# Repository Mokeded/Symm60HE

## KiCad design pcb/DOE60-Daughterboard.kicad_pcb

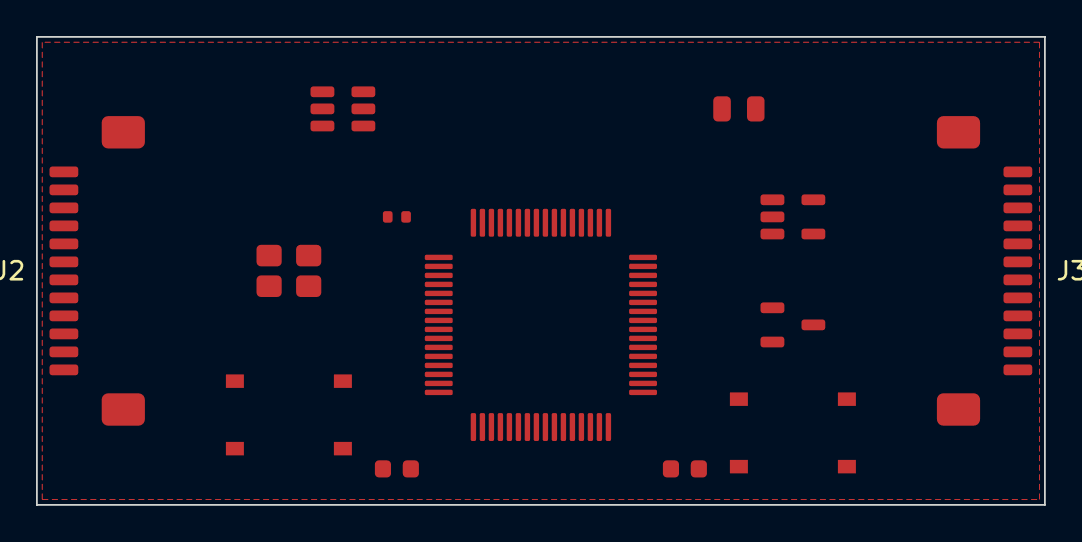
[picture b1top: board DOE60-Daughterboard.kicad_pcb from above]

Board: 2 copper layers, 56.0 x 26.0 mm, 13 parts (0 on the bottom side), 22 nets, no tracks yet.

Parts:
C1: 10u; C148_C_0603_1608Metric
C2: 1u; C148_C_0603_1608Metric
F1: 0.5A; F1_Fuse_0805_2012Metric
J2, J3: FFC_12P; FFC_12P_1.00mm_TopContact
R1: 12k; R3_R_0402_1005Metric
SW1, SW2: TS-1187A; SW1_SW_Push_1P1T_XKB_TS-1187A
U1: AT32F405RCT7; U4_LQFP-64_10x10mm_P0.5mm
U2: USBLC6-2SC6; U1_SOT-23-6
U3: TLV75733PDBV; U2_SOT-23-5
U4: XC6206P332MR; U3_SOT-23-3
Y1: 12MHz; Y1_Crystal_SMD_3225-4Pin_3.2x2.5mm

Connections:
+3V3A: J2.1, J3.1, U1.13, U4.2
+3V3D: C2.1, U1.1, U1.36, U3.5, U4.3
ADC_L1: J2.7, U1.17
ADC_L2: J2.9, U1.20
ADC_L3: J2.11, U1.21
ADC_L4: J2.12, U1.22
ADC_R1: J3.7, U1.23
ADC_R2: J3.9, U1.24
ADC_R3: J3.11, U1.25
ADC_R4: J3.12, U1.26
BOOT0: SW1.1, U1.60
GND: C1.2, C2.2, J2.2, J2.6, J2.8, J2.10, J3.2, J3.6, J3.8, J3.10, R1.2, SW1.2, SW2.2, U1.12, U1.31, U2.2, U3.2, U4.1, Y1.2, Y1.4
MUX_A0: J2.3, J3.3, U1.9
MUX_A1: J2.4, J3.4, U1.10
MUX_A2: J2.5, J3.5, U1.11
NRST: SW2.1, U1.7
USB_DM: U1.34, U2.3, U2.4
USB_DP: U1.35, U2.1, U2.6
USB_R: R1.1, U1.33
VBUS: C1.1, F1.2, U2.5, U3.1
XTAL_IN: U1.5, Y1.1
XTAL_OUT: U1.6, Y1.3

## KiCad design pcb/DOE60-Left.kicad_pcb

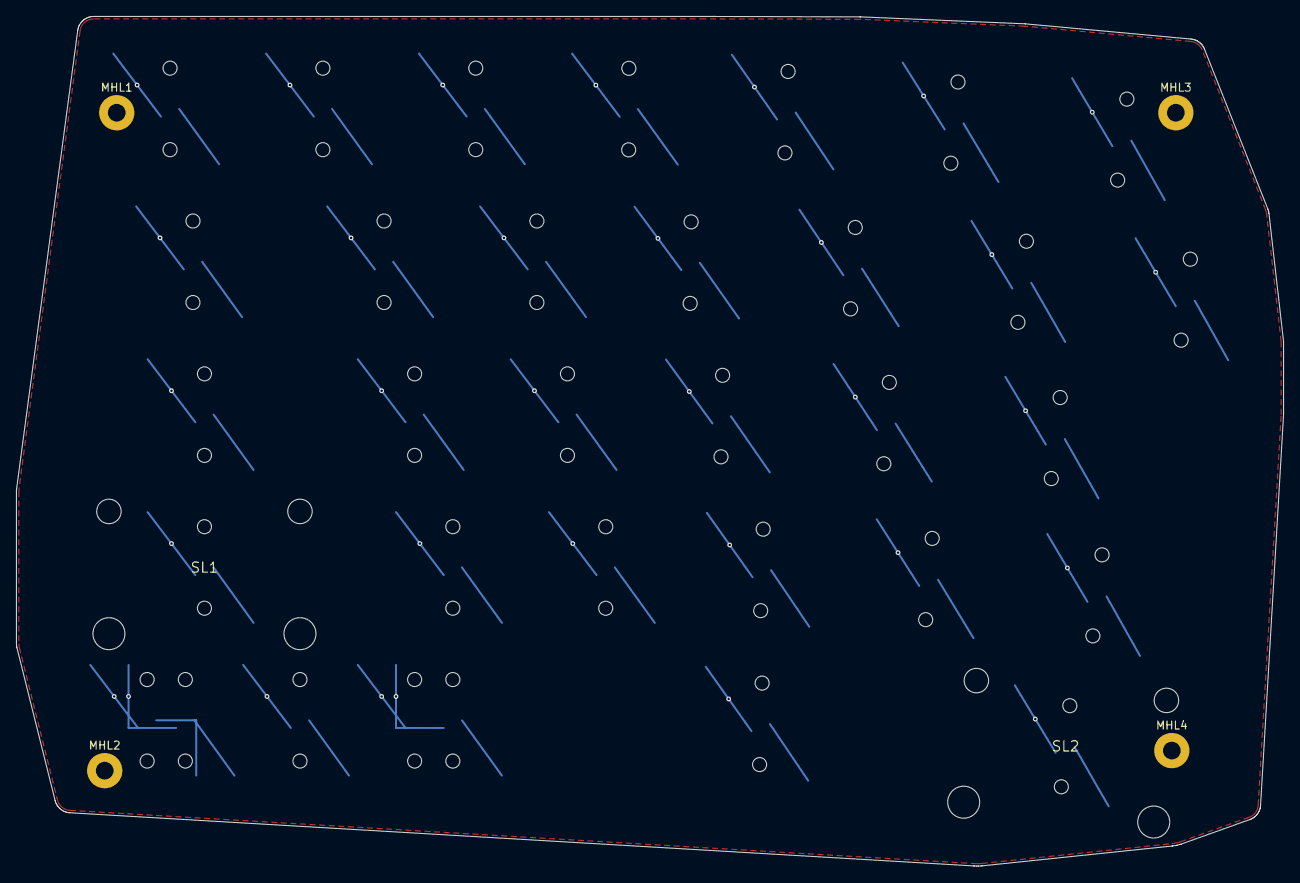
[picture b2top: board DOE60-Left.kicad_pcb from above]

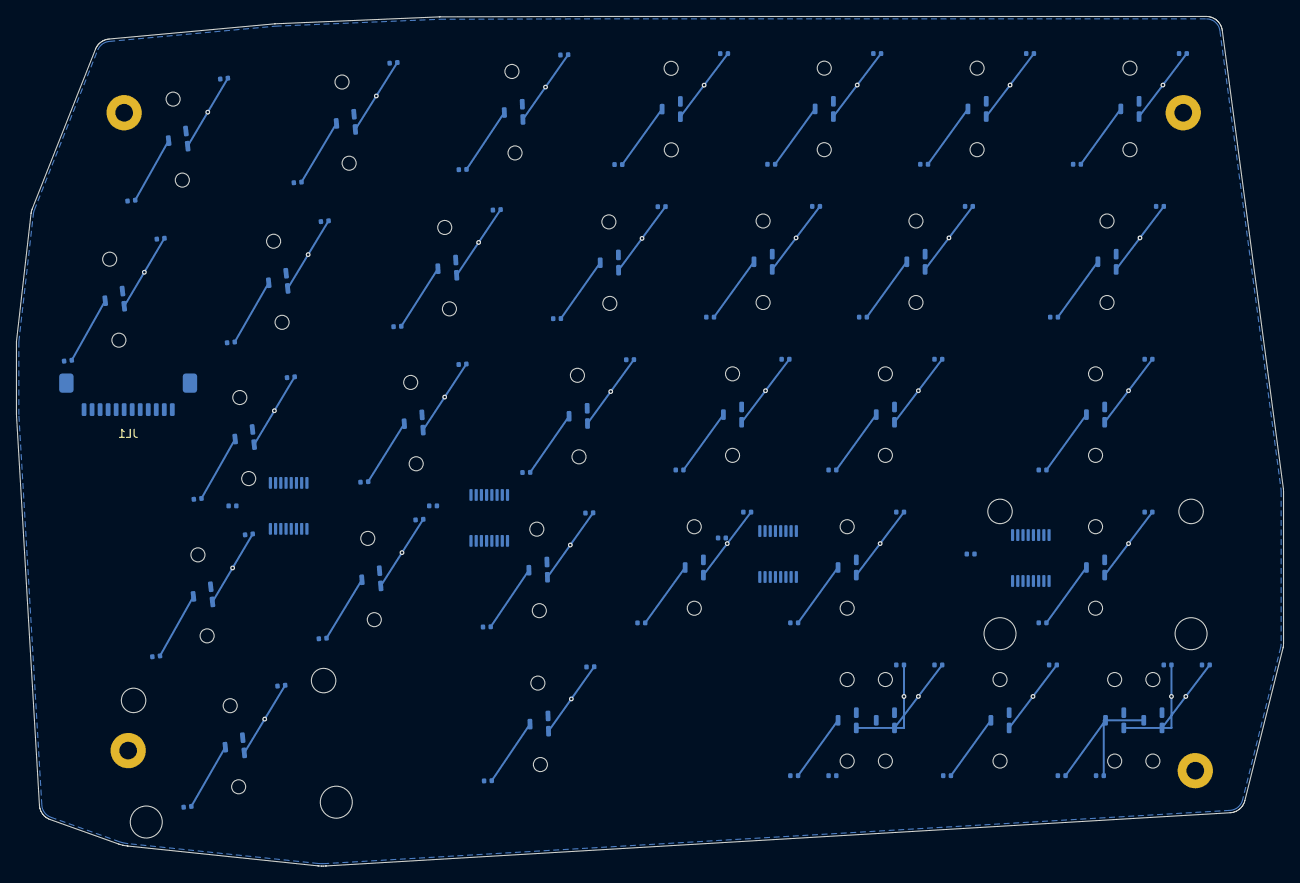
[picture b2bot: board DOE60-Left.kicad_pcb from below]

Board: 2 copper layers, 157.9 x 105.9 mm, 114 parts (108 on the bottom side), 40 nets.

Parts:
AML1, AML2, AML3, AML4: SN74LV4051A; AM1_TSSOP-16_4.4x5mm_P0.65mm
CL1A, CL2A, CL3A, CL4A, CL5A, CL6A, CL7A, CL8A, CL9A, CL10A, CL11A, CL12A, CL13A, CL14A, CL15A, CL16A, CL17A, CL18A, CL19A, CL20A, CL21A, CL22A, CL23A, CL24A, CL25A, CL26A, CL27A, CL28A, CL29A, CL30A, CL31A, CL32A, CL33A: 100n; C1_C_0402_1005Metric
CL1B, CL2B, CL3B, CL4B, CL5B, CL6B, CL7B, CL8B, CL9B, CL10B, CL11B, CL12B, CL13B, CL14B, CL15B, CL16B, CL17B, CL18B, CL19B, CL20B, CL21B, CL22B, CL23B, CL24B, CL25B, CL26B, CL27B, CL28B, CL29B, CL30B, CL31B, CL32B, CL33B: 4.7n; C1_C_0402_1005Metric
CML1, CML2, CML3, CML4: 100n; C1_C_0402_1005Metric
HEL1, HEL2, HEL3, HEL4, HEL5, HEL6, HEL7, HEL9, HEL10, HEL11, HEL12, HEL13, HEL14, HEL16, HEL17, HEL18, HEL19, HEL20, HEL22, HEL23, HEL24, HEL25, HEL26, HEL27, HEL29, HEL31: MT9102ET; HE_KEY_1.00u
HEL8, HEL28, HEL30, HEL32: MT9102ET; HE_KEY_1.50u
HEL15: MT9102ET; HE_KEY_1.75u
HEL21, HEL33: MT9102ET; HE_KEY_2.25u
JL1: FFC_12P; FFC_12P_1.00mm_TopContact
MHL1, MHL2, MHL3, MHL4: M2; MountingHole_2.2mm_M2_Pad
SL1, SL2: STAB_MX; STABILIZER_MX_2U

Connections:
+3V3A: AML1.16, AML2.16, AML3.16, AML4.16, CL1A.1, CL2A.1, CL3A.1, CL4A.1, CL5A.1, CL6A.1, CL7A.1, CL8A.1, CL9A.1, CL10A.1, CL11A.1, CL12A.1, CL13A.1, CL14A.1, CL15A.1, CL16A.1, CL17A.1, CL18A.1, CL19A.1, CL20A.1, CL21A.1, CL22A.1, CL23A.1, CL24A.1, CL25A.1, CL26A.1, CL27A.1, CL28A.1, CL29A.1, CL30A.1, CL31A.1, CL32A.1, CL33A.1, CML1.1, CML2.1, CML3.1, CML4.1, HEL1.1, HEL2.1, HEL3.1, HEL4.1, HEL5.1, HEL6.1, HEL7.1, HEL8.1, HEL9.1, HEL10.1, HEL11.1, HEL12.1, HEL13.1, HEL14.1, HEL15.1, HEL16.1, HEL17.1, HEL18.1, HEL19.1, HEL20.1, HEL21.1, HEL22.1, HEL23.1, HEL24.1, HEL25.1, HEL26.1, HEL27.1, HEL28.1, HEL29.1, HEL30.1, HEL31.1, HEL32.1, HEL33.1, JL1.1
ADC_L1: AML1.3, JL1.7
ADC_L2: AML2.3, JL1.9
ADC_L3: AML3.3, JL1.11
ADC_L4: AML4.3, JL1.12
GND: AML1.6, AML1.7, AML1.8, AML2.6, AML2.7, AML2.8, AML3.6, AML3.7, AML3.8, AML4.4, AML4.6, AML4.7, AML4.8, CL1A.2, CL1B.2, CL2A.2, CL2B.2, CL3A.2, CL3B.2, CL4A.2, CL4B.2, CL5A.2, CL5B.2, CL6A.2, CL6B.2, CL7A.2, CL7B.2, CL8A.2, CL8B.2, CL9A.2, CL9B.2, CL10A.2, CL10B.2, CL11A.2, CL11B.2, CL12A.2, CL12B.2, CL13A.2, CL13B.2, CL14A.2, CL14B.2, CL15A.2, CL15B.2, CL16A.2, CL16B.2, CL17A.2, CL17B.2, CL18A.2, CL18B.2, CL19A.2, CL19B.2, CL20A.2, CL20B.2, CL21A.2, CL21B.2, CL22A.2, CL22B.2, CL23A.2, CL23B.2, CL24A.2, CL24B.2, CL25A.2, CL25B.2, CL26A.2, CL26B.2, CL27A.2, CL27B.2, CL28A.2, CL28B.2, CL29A.2, CL29B.2, CL30A.2, CL30B.2, CL31A.2, CL31B.2, CL32A.2, CL32B.2, CL33A.2, CL33B.2, CML1.2, CML2.2, CML3.2, CML4.2, HEL1.2, HEL2.2, HEL3.2, HEL4.2, HEL5.2, HEL6.2, HEL7.2, HEL8.2, HEL9.2, HEL10.2, HEL11.2, HEL12.2, HEL13.2, HEL14.2, HEL15.2, HEL16.2, HEL17.2, HEL18.2, HEL19.2, HEL20.2, HEL21.2, HEL22.2, HEL23.2, HEL24.2, HEL25.2, HEL26.2, HEL27.2, HEL28.2, HEL29.2, HEL30.2, HEL31.2, HEL32.2, HEL33.2, JL1.2, JL1.6, JL1.8, JL1.10, MHL1.1, MHL2.1, MHL3.1, MHL4.1
HE_L01: AML1.13, CL1B.1, HEL1.3
HE_L02: AML1.14, CL2B.1, HEL2.3
HE_L03: AML1.15, CL3B.1, HEL3.3
HE_L04: AML1.12, CL4B.1, HEL4.3
HE_L05: AML1.1, CL5B.1, HEL5.3
HE_L06: AML1.5, CL6B.1, HEL6.3
HE_L07: AML1.2, CL7B.1, HEL7.3
HE_L08: AML1.4, CL8B.1, HEL8.3
HE_L09: AML2.13, CL9B.1, HEL9.3
HE_L10: AML2.14, CL10B.1, HEL10.3
HE_L11: AML2.15, CL11B.1, HEL11.3
HE_L12: AML2.12, CL12B.1, HEL12.3
HE_L13: AML2.1, CL13B.1, HEL13.3
HE_L14: AML2.5, CL14B.1, HEL14.3
HE_L15: AML2.2, CL15B.1, HEL15.3
HE_L16: AML2.4, CL16B.1, HEL16.3
HE_L17: AML3.13, CL17B.1, HEL17.3
HE_L18: AML3.14, CL18B.1, HEL18.3
HE_L19: AML3.15, CL19B.1, HEL19.3
HE_L20: AML3.12, CL20B.1, HEL20.3
HE_L21: AML3.1, CL21B.1, HEL21.3
HE_L22: AML3.5, CL22B.1, HEL22.3
HE_L23: AML3.2, CL23B.1, HEL23.3
HE_L24: AML3.4, CL24B.1, HEL24.3
HE_L25: AML4.13, CL25B.1, HEL25.3
HE_L26: AML4.14, CL26B.1, HEL26.3
HE_L27: AML4.15, CL27B.1, CL28B.1, HEL27.3, HEL28.3
HE_L28: AML4.12, CL29B.1, CL30B.1, HEL29.3, HEL30.3
HE_L29: AML4.1, CL31B.1, HEL31.3
HE_L30: AML4.5, CL32B.1, HEL32.3
HE_L31: AML4.2, CL33B.1, HEL33.3
MUX_A0: AML1.11, AML2.11, AML3.11, AML4.11, JL1.3
MUX_A1: AML1.10, AML2.10, AML3.10, AML4.10, JL1.4
MUX_A2: AML1.9, AML2.9, AML3.9, AML4.9, JL1.5

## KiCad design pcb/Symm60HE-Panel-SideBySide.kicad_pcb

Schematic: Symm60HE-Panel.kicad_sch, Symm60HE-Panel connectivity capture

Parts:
L-AML1, L-AML2, L-AML3, L-AML4, L-AML5: SN74LV4051A; AM1_TSSOP-16_4.4x5mm_P0.65mm
L-CL1A, L-CL2A, L-CL3A, L-CL4A, L-CL5A, L-CL6A, L-CL7A, L-CL8A, L-CL9A, L-CL10A, L-CL11A, L-CL12A, L-CL13A, L-CL14A, L-CL15A, L-CL16A, L-CL17A, L-CL18A, L-CL19A, L-CL20A, L-CL21A, L-CL22A, L-CL23A, L-CL24A, L-CL25A, L-CL26A, L-CL27A, L-CL28A, L-CL29A, L-CL30A, L-CL31A, L-CL32A, L-CL33A: 100n; C1_C_0402_1005Metric
L-CL1B, L-CL2B, L-CL3B, L-CL4B, L-CL5B, L-CL6B, L-CL7B, L-CL8B, L-CL9B, L-CL10B, L-CL11B, L-CL12B, L-CL13B, L-CL14B, L-CL15B, L-CL16B, L-CL17B, L-CL18B, L-CL19B, L-CL20B, L-CL21B, L-CL22B, L-CL23B, L-CL24B, L-CL25B, L-CL26B, L-CL27B, L-CL28B, L-CL29B, L-CL30B, L-CL31B, L-CL32B, L-CL33B: 4.7n; C1_C_0402_1005Metric
L-CML1, L-CML2, L-CML3, L-CML4, L-CML5: 100n; C1_C_0402_1005Metric
L-CRGBL1, L-CRGBL2, L-CRGBL3, L-CRGBL4, L-CRGBL5, L-CRGBL6, L-CRGBL7, L-CRGBL8, L-CRGBL9, L-CRGBL10, L-CRGBL11, L-CRGBL12, L-CRGBL13, L-CRGBL14, L-CRGBL15, L-CRGBL16, L-CRGBL17, L-CRGBL18, L-CRGBL19, L-CRGBL20, L-CRGBL21, L-CRGBL22, L-CRGBL23, L-CRGBL24, L-CRGBL25, L-CRGBL26, L-CRGBL27, L-CRGBL29, L-CRGBL30, L-CRGBL31, L-CRGBL33: 100n; C1_C_0402_1005Metric
L-DL1, L-DL2, L-DL3, L-DL4, L-DL5, L-DL6, L-DL7, L-DL8, L-DL9, L-DL10, L-DL11, L-DL12, L-DL13, L-DL14, L-DL15, L-DL16, L-DL17, L-DL18, L-DL19, L-DL20, L-DL21, L-DL22, L-DL23, L-DL24, L-DL25, L-DL26, L-DL27, L-DL29, L-DL30, L-DL31, L-DL33: SK6812MINI-E; SK6812MINI-E_ReverseMount
L-HEL1, L-HEL2, L-HEL3, L-HEL4, L-HEL5, L-HEL6, L-HEL7, L-HEL9, L-HEL10, L-HEL11, L-HEL12, L-HEL13, L-HEL14, L-HEL16, L-HEL17, L-HEL18, L-HEL19, L-HEL20, L-HEL22, L-HEL23, L-HEL24, L-HEL25, L-HEL26, L-HEL27, L-HEL29, L-HEL31: MT9102ET; HE_KEY_1.00u
L-HEL8, L-HEL28, L-HEL30, L-HEL32: MT9102ET; HE_KEY_1.50u
L-HEL15: MT9102ET; HE_KEY_1.75u
L-HEL21, L-HEL33: MT9102ET; HE_KEY_2.25u
L-JL1: FFC_12P; FFC_12P_1.00mm_TopContact
L-RBPL29: 0R_DNP; R3_R_0402_1005Metric
R-AMR1, R-AMR2, R-AMR3, R-AMR4, R-AMR5: SN74LV4051A; AM1_TSSOP-16_4.4x5mm_P0.65mm
R-CMR1, R-CMR2, R-CMR3, R-CMR4, R-CMR5: 100n; C1_C_0402_1005Metric
R-CR1A, R-CR2A, R-CR3A, R-CR4A, R-CR5A, R-CR6A, R-CR7A, R-CR8A, R-CR9A, R-CR10A, R-CR11A, R-CR12A, R-CR13A, R-CR14A, R-CR15A, R-CR16A, R-CR17A, R-CR18A, R-CR19A, R-CR20A, R-CR21A, R-CR22A, R-CR23A, R-CR24A, R-CR25A, R-CR26A, R-CR27A, R-CR28A, R-CR29A, R-CR30A, R-CR31A, R-CR32A, R-CR33A, R-CR34A, R-CR35A, R-CR36A: 100n; C1_C_0402_1005Metric
R-CR1B, R-CR2B, R-CR3B, R-CR4B, R-CR5B, R-CR6B, R-CR7B, R-CR8B, R-CR9B, R-CR10B, R-CR11B, R-CR12B, R-CR13B, R-CR14B, R-CR15B, R-CR16B, R-CR17B, R-CR18B, R-CR19B, R-CR20B, R-CR21B, R-CR22B, R-CR23B, R-CR24B, R-CR25B, R-CR26B, R-CR27B, R-CR28B, R-CR29B, R-CR30B, R-CR31B, R-CR32B, R-CR33B, R-CR34B, R-CR35B, R-CR36B: 4.7n; C1_C_0402_1005Metric
R-CRGBR1, R-CRGBR2, R-CRGBR3, R-CRGBR4, R-CRGBR5, R-CRGBR6, R-CRGBR7, R-CRGBR8, R-CRGBR9, R-CRGBR10, R-CRGBR11, R-CRGBR12, R-CRGBR13, R-CRGBR14, R-CRGBR15, R-CRGBR16, R-CRGBR17, R-CRGBR18, R-CRGBR19, R-CRGBR20, R-CRGBR21, R-CRGBR22, R-CRGBR23, R-CRGBR24, R-CRGBR25, R-CRGBR26, R-CRGBR27, R-CRGBR28, R-CRGBR29, R-CRGBR31, R-CRGBR32, R-CRGBR33, R-CRGBR34, R-CRGBR36: 100n; C1_C_0402_1005Metric
R-DR1, R-DR2, R-DR3, R-DR4, R-DR5, R-DR6, R-DR7, R-DR8, R-DR9, R-DR10, R-DR11, R-DR12, R-DR13, R-DR14, R-DR15, R-DR16, R-DR17, R-DR18, R-DR19, R-DR20, R-DR21, R-DR22, R-DR23, R-DR24, R-DR25, R-DR26, R-DR27, R-DR28, R-DR29, R-DR31, R-DR32, R-DR33, R-DR34, R-DR36: SK6812MINI-E; SK6812MINI-E_ReverseMount
R-HER1, R-HER2, R-HER3, R-HER5, R-HER6, R-HER7, R-HER8, R-HER9, R-HER10, R-HER12, R-HER13, R-HER14, R-HER15, R-HER16, R-HER17, R-HER19, R-HER20, R-HER21, R-HER22, R-HER23, R-HER24, R-HER27, R-HER28, R-HER29, R-HER30, R-HER32, R-HER34: MT9102ET; HE_KEY_1.00u
R-HER4: MT9102ET; HE_KEY_2.00u
R-HER11, R-HER31, R-HER33, R-HER35: MT9102ET; HE_KEY_1.50u
R-HER18: MT9102ET; HE_KEY_1.75u
R-HER25, R-HER36: MT9102ET; HE_KEY_2.25u
R-HER26: MT9102ET; HE_KEY_1.25u
R-JR1: FFC_12P; FFC_12P_1.00mm_TopContact
R-RBPR5, R-RBPR24, R-RBPR31: 0R_DNP; R3_R_0402_1005Metric

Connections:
/L/+3V3A: L-AML1.16 (/L/+3V3A), L-AML2.16 (/L/+3V3A), L-AML3.16 (/L/+3V3A), L-AML4.16 (/L/+3V3A), L-AML5.16 (/L/+3V3A), L-CL1A.1 (/L/+3V3A), L-CL2A.1 (/L/+3V3A), L-CL3A.1 (/L/+3V3A), L-CL4A.1 (/L/+3V3A), L-CL5A.1 (/L/+3V3A), L-CL6A.1 (/L/+3V3A), L-CL7A.1 (/L/+3V3A), L-CL8A.1 (/L/+3V3A), L-CL9A.1 (/L/+3V3A), L-CL10A.1 (/L/+3V3A), L-CL11A.1 (/L/+3V3A), L-CL12A.1 (/L/+3V3A), L-CL13A.1 (/L/+3V3A), L-CL14A.1 (/L/+3V3A), L-CL15A.1 (/L/+3V3A), L-CL16A.1 (/L/+3V3A), L-CL17A.1 (/L/+3V3A), L-CL18A.1 (/L/+3V3A), L-CL19A.1 (/L/+3V3A), L-CL20A.1 (/L/+3V3A), L-CL21A.1 (/L/+3V3A), L-CL22A.1 (/L/+3V3A), L-CL23A.1 (/L/+3V3A), L-CL24A.1 (/L/+3V3A), L-CL25A.1 (/L/+3V3A), L-CL26A.1 (/L/+3V3A), L-CL27A.1 (/L/+3V3A), L-CL28A.1 (/L/+3V3A), L-CL29A.1 (/L/+3V3A), L-CL30A.1 (/L/+3V3A), L-CL31A.1 (/L/+3V3A), L-CL32A.1 (/L/+3V3A), L-CL33A.1 (/L/+3V3A), L-CML1.1 (/L/+3V3A), L-CML2.1 (/L/+3V3A), L-CML3.1 (/L/+3V3A), L-CML4.1 (/L/+3V3A), L-CML5.1 (/L/+3V3A), L-HEL1.1 (/L/+3V3A), L-HEL2.1 (/L/+3V3A), L-HEL3.1 (/L/+3V3A), L-HEL4.1 (/L/+3V3A), L-HEL5.1 (/L/+3V3A), L-HEL6.1 (/L/+3V3A), L-HEL7.1 (/L/+3V3A), L-HEL8.1 (/L/+3V3A), L-HEL9.1 (/L/+3V3A), L-HEL10.1 (/L/+3V3A), L-HEL11.1 (/L/+3V3A), L-HEL12.1 (/L/+3V3A), L-HEL13.1 (/L/+3V3A), L-HEL14.1 (/L/+3V3A), L-HEL15.1 (/L/+3V3A), L-HEL16.1 (/L/+3V3A), L-HEL17.1 (/L/+3V3A), L-HEL18.1 (/L/+3V3A), L-HEL19.1 (/L/+3V3A), L-HEL20.1 (/L/+3V3A), L-HEL21.1 (/L/+3V3A), L-HEL22.1 (/L/+3V3A), L-HEL23.1 (/L/+3V3A), L-HEL24.1 (/L/+3V3A), L-HEL25.1 (/L/+3V3A), L-HEL26.1 (/L/+3V3A), L-HEL27.1 (/L/+3V3A), L-HEL28.1 (/L/+3V3A), L-HEL29.1 (/L/+3V3A), L-HEL30.1 (/L/+3V3A), L-HEL31.1 (/L/+3V3A), L-HEL32.1 (/L/+3V3A), L-HEL33.1 (/L/+3V3A), L-JL1.12 (/L/+3V3A)
/L/ADC_L1: L-AML1.3 (/L/ADC_L1), L-JL1.6 (/L/ADC_L1)
/L/ADC_L2: L-AML2.3 (/L/ADC_L2), L-JL1.4 (/L/ADC_L2)
/L/ADC_L3: L-AML3.3 (/L/ADC_L3), L-JL1.2 (/L/ADC_L3)
/L/ADC_L4: L-AML4.3 (/L/ADC_L4), L-JL1.1 (/L/ADC_L4)
/L/ADC_L5: L-AML5.3 (/L/ADC_L5), L-JL1.11 (/L/ADC_L5)
/L/GND: L-AML1.6 (/L/GND), L-AML1.7 (/L/GND), L-AML1.8 (/L/GND), L-AML2.6 (/L/GND), L-AML2.7 (/L/GND), L-AML2.8 (/L/GND), L-AML3.6 (/L/GND), L-AML3.7 (/L/GND), L-AML3.8 (/L/GND), L-AML4.4 (/L/GND), L-AML4.6 (/L/GND), L-AML4.7 (/L/GND), L-AML4.8 (/L/GND), L-AML5.1 (/L/GND), L-AML5.2 (/L/GND), L-AML5.4 (/L/GND), L-AML5.5 (/L/GND), L-AML5.6 (/L/GND), L-AML5.7 (/L/GND), L-AML5.8 (/L/GND), L-AML5.12 (/L/GND), L-AML5.15 (/L/GND), L-CL1A.2 (/L/GND), L-CL1B.2 (/L/GND), L-CL2A.2 (/L/GND), L-CL2B.2 (/L/GND), L-CL3A.2 (/L/GND), L-CL3B.2 (/L/GND), L-CL4A.2 (/L/GND), L-CL4B.2 (/L/GND), L-CL5A.2 (/L/GND), L-CL5B.2 (/L/GND), L-CL6A.2 (/L/GND), L-CL6B.2 (/L/GND), L-CL7A.2 (/L/GND), L-CL7B.2 (/L/GND), L-CL8A.2 (/L/GND), L-CL8B.2 (/L/GND), L-CL9A.2 (/L/GND), L-CL9B.2 (/L/GND), L-CL10A.2 (/L/GND), L-CL10B.2 (/L/GND), L-CL11A.2 (/L/GND), L-CL11B.2 (/L/GND), L-CL12A.2 (/L/GND), L-CL12B.2 (/L/GND), L-CL13A.2 (/L/GND), L-CL13B.2 (/L/GND), L-CL14A.2 (/L/GND), L-CL14B.2 (/L/GND), L-CL15A.2 (/L/GND), L-CL15B.2 (/L/GND), L-CL16A.2 (/L/GND), L-CL16B.2 (/L/GND), L-CL17A.2 (/L/GND), L-CL17B.2 (/L/GND), L-CL18A.2 (/L/GND), L-CL18B.2 (/L/GND), L-CL19A.2 (/L/GND), L-CL19B.2 (/L/GND), L-CL20A.2 (/L/GND), L-CL20B.2 (/L/GND), L-CL21A.2 (/L/GND), L-CL21B.2 (/L/GND), L-CL22A.2 (/L/GND), L-CL22B.2 (/L/GND), L-CL23A.2 (/L/GND), L-CL23B.2 (/L/GND), L-CL24A.2 (/L/GND), L-CL24B.2 (/L/GND), L-CL25A.2 (/L/GND), L-CL25B.2 (/L/GND), L-CL26A.2 (/L/GND), L-CL26B.2 (/L/GND), L-CL27A.2 (/L/GND), L-CL27B.2 (/L/GND), L-CL28A.2 (/L/GND), L-CL28B.2 (/L/GND), L-CL29A.2 (/L/GND), L-CL29B.2 (/L/GND), L-CL30A.2 (/L/GND), L-CL30B.2 (/L/GND), L-CL31A.2 (/L/GND), L-CL31B.2 (/L/GND), L-CL32A.2 (/L/GND), L-CL32B.2 (/L/GND), L-CL33A.2 (/L/GND), L-CL33B.2 (/L/GND), L-CML1.2 (/L/GND), L-CML2.2 (/L/GND), L-CML3.2 (/L/GND), L-CML4.2 (/L/GND), L-CML5.2 (/L/GND), L-CRGBL1.2 (/L/GND), L-CRGBL2.2 (/L/GND), L-CRGBL3.2 (/L/GND), L-CRGBL4.2 (/L/GND), L-CRGBL5.2 (/L/GND), L-CRGBL6.2 (/L/GND), L-CRGBL7.2 (/L/GND), L-CRGBL8.2 (/L/GND), L-CRGBL9.2 (/L/GND), L-CRGBL10.2 (/L/GND), L-CRGBL11.2 (/L/GND), L-CRGBL12.2 (/L/GND), L-CRGBL13.2 (/L/GND), L-CRGBL14.2 (/L/GND), L-CRGBL15.2 (/L/GND), L-CRGBL16.2 (/L/GND), L-CRGBL17.2 (/L/GND), L-CRGBL18.2 (/L/GND), L-CRGBL19.2 (/L/GND), L-CRGBL20.2 (/L/GND), L-CRGBL21.2 (/L/GND), L-CRGBL22.2 (/L/GND), L-CRGBL23.2 (/L/GND), L-CRGBL24.2 (/L/GND), L-CRGBL25.2 (/L/GND), L-CRGBL26.2 (/L/GND), L-CRGBL27.2 (/L/GND), L-CRGBL29.2 (/L/GND), L-CRGBL30.2 (/L/GND), L-CRGBL31.2 (/L/GND), L-CRGBL33.2 (/L/GND), L-DL1.1 (/L/GND), L-DL2.1 (/L/GND), L-DL3.1 (/L/GND), L-DL4.1 (/L/GND), L-DL5.1 (/L/GND), L-DL6.1 (/L/GND), L-DL7.1 (/L/GND), L-DL8.1 (/L/GND), L-DL9.1 (/L/GND), L-DL10.1 (/L/GND), L-DL11.1 (/L/GND), L-DL12.1 (/L/GND), L-DL13.1 (/L/GND), L-DL14.1 (/L/GND), L-DL15.1 (/L/GND), L-DL16.1 (/L/GND), L-DL17.1 (/L/GND), L-DL18.1 (/L/GND), L-DL19.1 (/L/GND), L-DL20.1 (/L/GND), L-DL21.1 (/L/GND), L-DL22.1 (/L/GND), L-DL23.1 (/L/GND), L-DL24.1 (/L/GND), L-DL25.1 (/L/GND), L-DL26.1 (/L/GND), L-DL27.1 (/L/GND), L-DL29.1 (/L/GND), L-DL30.1 (/L/GND), L-DL31.1 (/L/GND), L-DL33.1 (/L/GND), L-HEL1.2 (/L/GND), L-HEL2.2 (/L/GND), L-HEL3.2 (/L/GND), L-HEL4.2 (/L/GND), L-HEL5.2 (/L/GND), L-HEL6.2 (/L/GND), L-HEL7.2 (/L/GND), L-HEL8.2 (/L/GND), L-HEL9.2 (/L/GND), L-HEL10.2 (/L/GND), L-HEL11.2 (/L/GND), L-HEL12.2 (/L/GND), L-HEL13.2 (/L/GND), L-HEL14.2 (/L/GND), L-HEL15.2 (/L/GND), L-HEL16.2 (/L/GND), L-HEL17.2 (/L/GND), L-HEL18.2 (/L/GND), L-HEL19.2 (/L/GND), L-HEL20.2 (/L/GND), L-HEL21.2 (/L/GND), L-HEL22.2 (/L/GND), L-HEL23.2 (/L/GND), L-HEL24.2 (/L/GND), L-HEL25.2 (/L/GND), L-HEL26.2 (/L/GND), L-HEL27.2 (/L/GND), L-HEL28.2 (/L/GND), L-HEL29.2 (/L/GND), L-HEL30.2 (/L/GND), L-HEL31.2 (/L/GND), L-HEL32.2 (/L/GND), L-HEL33.2 (/L/GND), L-JL1.5 (/L/GND)
/L/HE_L01: L-AML1.13 (/L/HE_L01), L-CL1B.1 (/L/HE_L01), L-HEL1.3 (/L/HE_L01)
/L/HE_L02: L-AML1.14 (/L/HE_L02), L-CL2B.1 (/L/HE_L02), L-HEL2.3 (/L/HE_L02)
/L/HE_L03: L-AML1.15 (/L/HE_L03), L-CL3B.1 (/L/HE_L03), L-HEL3.3 (/L/HE_L03)
/L/HE_L04: L-AML1.12 (/L/HE_L04), L-CL4B.1 (/L/HE_L04), L-HEL4.3 (/L/HE_L04)
/L/HE_L05: L-AML1.1 (/L/HE_L05), L-CL5B.1 (/L/HE_L05), L-HEL5.3 (/L/HE_L05)
/L/HE_L06: L-AML1.5 (/L/HE_L06), L-CL6B.1 (/L/HE_L06), L-HEL6.3 (/L/HE_L06)
/L/HE_L07: L-AML1.2 (/L/HE_L07), L-CL7B.1 (/L/HE_L07), L-HEL7.3 (/L/HE_L07)
/L/HE_L08: L-AML1.4 (/L/HE_L08), L-CL8B.1 (/L/HE_L08), L-HEL8.3 (/L/HE_L08)
/L/HE_L09: L-AML2.13 (/L/HE_L09), L-CL9B.1 (/L/HE_L09), L-HEL9.3 (/L/HE_L09)
/L/HE_L10: L-AML2.14 (/L/HE_L10), L-CL10B.1 (/L/HE_L10), L-HEL10.3 (/L/HE_L10)
/L/HE_L11: L-AML2.15 (/L/HE_L11), L-CL11B.1 (/L/HE_L11), L-HEL11.3 (/L/HE_L11)
/L/HE_L12: L-AML2.12 (/L/HE_L12), L-CL12B.1 (/L/HE_L12), L-HEL12.3 (/L/HE_L12)
/L/HE_L13: L-AML2.1 (/L/HE_L13), L-CL13B.1 (/L/HE_L13), L-HEL13.3 (/L/HE_L13)
/L/HE_L14: L-AML2.5 (/L/HE_L14), L-CL14B.1 (/L/HE_L14), L-HEL14.3 (/L/HE_L14)
/L/HE_L15: L-AML2.2 (/L/HE_L15), L-CL15B.1 (/L/HE_L15), L-HEL15.3 (/L/HE_L15)
/L/HE_L16: L-AML2.4 (/L/HE_L16), L-CL16B.1 (/L/HE_L16), L-HEL16.3 (/L/HE_L16)
/L/HE_L17: L-AML3.13 (/L/HE_L17), L-CL17B.1 (/L/HE_L17), L-HEL17.3 (/L/HE_L17)
/L/HE_L18: L-AML3.14 (/L/HE_L18), L-CL18B.1 (/L/HE_L18), L-HEL18.3 (/L/HE_L18)
/L/HE_L19: L-AML3.15 (/L/HE_L19), L-CL19B.1 (/L/HE_L19), L-HEL19.3 (/L/HE_L19)
/L/HE_L20: L-AML3.12 (/L/HE_L20), L-CL20B.1 (/L/HE_L20), L-HEL20.3 (/L/HE_L20)
/L/HE_L21: L-AML3.1 (/L/HE_L21), L-CL21B.1 (/L/HE_L21), L-HEL21.3 (/L/HE_L21)
/L/HE_L22: L-AML3.5 (/L/HE_L22), L-CL22B.1 (/L/HE_L22), L-HEL22.3 (/L/HE_L22)
/L/HE_L23: L-AML3.2 (/L/HE_L23), L-CL23B.1 (/L/HE_L23), L-HEL23.3 (/L/HE_L23)
/L/HE_L24: L-AML3.4 (/L/HE_L24), L-CL24B.1 (/L/HE_L24), L-HEL24.3 (/L/HE_L24)
/L/HE_L25: L-AML4.13 (/L/HE_L25), L-CL25B.1 (/L/HE_L25), L-HEL25.3 (/L/HE_L25)
/L/HE_L26: L-AML4.14 (/L/HE_L26), L-CL26B.1 (/L/HE_L26), L-HEL26.3 (/L/HE_L26)
/L/HE_L27: L-AML4.15 (/L/HE_L27), L-CL27B.1 (/L/HE_L27), L-HEL27.3 (/L/HE_L27)
/L/HE_L28: L-AML4.12 (/L/HE_L28), L-CL29B.1 (/L/HE_L28), L-HEL29.3 (/L/HE_L28)
/L/HE_L29: L-AML4.1 (/L/HE_L29), L-CL31B.1 (/L/HE_L29), L-HEL31.3 (/L/HE_L29)
/L/HE_L30: L-AML4.5 (/L/HE_L30), L-CL32B.1 (/L/HE_L30), L-HEL32.3 (/L/HE_L30)
/L/HE_L31: L-AML4.2 (/L/HE_L31), L-CL33B.1 (/L/HE_L31), L-HEL33.3 (/L/HE_L31)
/L/HE_L32: L-AML5.13 (/L/HE_L32), L-CL28B.1 (/L/HE_L32), L-HEL28.3 (/L/HE_L32)
/L/HE_L33: L-AML5.14 (/L/HE_L33), L-CL30B.1 (/L/HE_L33), L-HEL30.3 (/L/HE_L33)
/L/MUX_A0: L-AML1.11 (/L/MUX_A0), L-AML2.11 (/L/MUX_A0), L-AML3.11 (/L/MUX_A0), L-AML4.11 (/L/MUX_A0), L-AML5.11 (/L/MUX_A0), L-JL1.10 (/L/MUX_A0)
/L/MUX_A1: L-AML1.10 (/L/MUX_A1), L-AML2.10 (/L/MUX_A1), L-AML3.10 (/L/MUX_A1), L-AML4.10 (/L/MUX_A1), L-AML5.10 (/L/MUX_A1), L-JL1.9 (/L/MUX_A1)
/L/MUX_A2: L-AML1.9 (/L/MUX_A2), L-AML2.9 (/L/MUX_A2), L-AML3.9 (/L/MUX_A2), L-AML4.9 (/L/MUX_A2), L-AML5.9 (/L/MUX_A2), L-JL1.8 (/L/MUX_A2)
/L/RGB_L: L-DL1.2 (/L/RGB_L), L-JL1.3 (/L/RGB_L)
/L/RGB_L_01: L-DL1.4 (/L/RGB_L_01), L-DL2.2 (/L/RGB_L_01)
/L/RGB_L_02: L-DL2.4 (/L/RGB_L_02), L-DL3.2 (/L/RGB_L_02)
/L/RGB_L_03: L-DL3.4 (/L/RGB_L_03), L-DL4.2 (/L/RGB_L_03)
/L/RGB_L_04: L-DL4.4 (/L/RGB_L_04), L-DL5.2 (/L/RGB_L_04)
/L/RGB_L_05: L-DL5.4 (/L/RGB_L_05), L-DL6.2 (/L/RGB_L_05)
/L/RGB_L_06: L-DL6.4 (/L/RGB_L_06), L-DL7.2 (/L/RGB_L_06)
/L/RGB_L_07: L-DL7.4 (/L/RGB_L_07), L-DL8.2 (/L/RGB_L_07)
/L/RGB_L_08: L-DL8.4 (/L/RGB_L_08), L-DL9.2 (/L/RGB_L_08)
/L/RGB_L_09: L-DL9.4 (/L/RGB_L_09), L-DL10.2 (/L/RGB_L_09)
/L/RGB_L_10: L-DL10.4 (/L/RGB_L_10), L-DL11.2 (/L/RGB_L_10)
/L/RGB_L_11: L-DL11.4 (/L/RGB_L_11), L-DL12.2 (/L/RGB_L_11)
/L/RGB_L_12: L-DL12.4 (/L/RGB_L_12), L-DL13.2 (/L/RGB_L_12)
/L/RGB_L_13: L-DL13.4 (/L/RGB_L_13), L-DL14.2 (/L/RGB_L_13)
/L/RGB_L_14: L-DL14.4 (/L/RGB_L_14), L-DL15.2 (/L/RGB_L_14)
/L/RGB_L_15: L-DL15.4 (/L/RGB_L_15), L-DL16.2 (/L/RGB_L_15)
/L/RGB_L_16: L-DL16.4 (/L/RGB_L_16), L-DL17.2 (/L/RGB_L_16)
/L/RGB_L_17: L-DL17.4 (/L/RGB_L_17), L-DL18.2 (/L/RGB_L_17)
/L/RGB_L_18: L-DL18.4 (/L/RGB_L_18), L-DL19.2 (/L/RGB_L_18)
/L/RGB_L_19: L-DL19.4 (/L/RGB_L_19), L-DL20.2 (/L/RGB_L_19)
/L/RGB_L_20: L-DL20.4 (/L/RGB_L_20), L-DL21.2 (/L/RGB_L_20)
/L/RGB_L_21: L-DL21.4 (/L/RGB_L_21), L-DL22.2 (/L/RGB_L_21)
/L/RGB_L_22: L-DL22.4 (/L/RGB_L_22), L-DL23.2 (/L/RGB_L_22)
/L/RGB_L_23: L-DL23.4 (/L/RGB_L_23), L-DL24.2 (/L/RGB_L_23)
/L/RGB_L_24: L-DL24.4 (/L/RGB_L_24), L-DL25.2 (/L/RGB_L_24)
/L/RGB_L_25: L-DL25.4 (/L/RGB_L_25), L-DL26.2 (/L/RGB_L_25)
/L/RGB_L_26: L-DL26.4 (/L/RGB_L_26), L-DL27.2 (/L/RGB_L_26)
/L/RGB_L_27: L-DL27.4 (/L/RGB_L_27), L-DL33.2 (/L/RGB_L_27)
/L/RGB_L_28: L-DL29.2 (/L/RGB_L_28), L-DL33.4 (/L/RGB_L_28), L-RBPL29.1 (/L/RGB_L_28)
/L/RGB_L_29: L-DL29.4 (/L/RGB_L_29), L-DL30.2 (/L/RGB_L_29), L-RBPL29.2 (/L/RGB_L_29)
/L/RGB_L_30: L-DL30.4 (/L/RGB_L_30), L-DL31.2 (/L/RGB_L_30)
/L/RGB_L_END: L-DL31.4 (/L/RGB_L_END)
/L/VBUS: L-CRGBL1.1 (/L/VBUS), L-CRGBL2.1 (/L/VBUS), L-CRGBL3.1 (/L/VBUS), L-CRGBL4.1 (/L/VBUS), L-CRGBL5.1 (/L/VBUS), L-CRGBL6.1 (/L/VBUS), L-CRGBL7.1 (/L/VBUS), L-CRGBL8.1 (/L/VBUS), L-CRGBL9.1 (/L/VBUS), L-CRGBL10.1 (/L/VBUS), L-CRGBL11.1 (/L/VBUS), L-CRGBL12.1 (/L/VBUS), L-CRGBL13.1 (/L/VBUS), L-CRGBL14.1 (/L/VBUS), L-CRGBL15.1 (/L/VBUS), L-CRGBL16.1 (/L/VBUS), L-CRGBL17.1 (/L/VBUS), L-CRGBL18.1 (/L/VBUS), L-CRGBL19.1 (/L/VBUS), L-CRGBL20.1 (/L/VBUS), L-CRGBL21.1 (/L/VBUS), L-CRGBL22.1 (/L/VBUS), L-CRGBL23.1 (/L/VBUS), L-CRGBL24.1 (/L/VBUS), L-CRGBL25.1 (/L/VBUS), L-CRGBL26.1 (/L/VBUS), L-CRGBL27.1 (/L/VBUS), L-CRGBL29.1 (/L/VBUS), L-CRGBL30.1 (/L/VBUS), L-CRGBL31.1 (/L/VBUS), L-CRGBL33.1 (/L/VBUS), L-DL1.3 (/L/VBUS), L-DL2.3 (/L/VBUS), L-DL3.3 (/L/VBUS), L-DL4.3 (/L/VBUS), L-DL5.3 (/L/VBUS), L-DL6.3 (/L/VBUS), L-DL7.3 (/L/VBUS), L-DL8.3 (/L/VBUS), L-DL9.3 (/L/VBUS), L-DL10.3 (/L/VBUS), L-DL11.3 (/L/VBUS), L-DL12.3 (/L/VBUS), L-DL13.3 (/L/VBUS), L-DL14.3 (/L/VBUS), L-DL15.3 (/L/VBUS), L-DL16.3 (/L/VBUS), L-DL17.3 (/L/VBUS), L-DL18.3 (/L/VBUS), L-DL19.3 (/L/VBUS), L-DL20.3 (/L/VBUS), L-DL21.3 (/L/VBUS), L-DL22.3 (/L/VBUS), L-DL23.3 (/L/VBUS), L-DL24.3 (/L/VBUS), L-DL25.3 (/L/VBUS), L-DL26.3 (/L/VBUS), L-DL27.3 (/L/VBUS), L-DL29.3 (/L/VBUS), L-DL30.3 (/L/VBUS), L-DL31.3 (/L/VBUS), L-DL33.3 (/L/VBUS), L-JL1.7 (/L/VBUS)
/R/+3V3A: R-AMR1.16 (/R/+3V3A), R-AMR2.16 (/R/+3V3A), R-AMR3.16 (/R/+3V3A), R-AMR4.16 (/R/+3V3A), R-AMR5.16 (/R/+3V3A), R-CMR1.1 (/R/+3V3A), R-CMR2.1 (/R/+3V3A), R-CMR3.1 (/R/+3V3A), R-CMR4.1 (/R/+3V3A), R-CMR5.1 (/R/+3V3A), R-CR1A.1 (/R/+3V3A), R-CR2A.1 (/R/+3V3A), R-CR3A.1 (/R/+3V3A), R-CR4A.1 (/R/+3V3A), R-CR5A.1 (/R/+3V3A), R-CR6A.1 (/R/+3V3A), R-CR7A.1 (/R/+3V3A), R-CR8A.1 (/R/+3V3A), R-CR9A.1 (/R/+3V3A), R-CR10A.1 (/R/+3V3A), R-CR11A.1 (/R/+3V3A), R-CR12A.1 (/R/+3V3A), R-CR13A.1 (/R/+3V3A), R-CR14A.1 (/R/+3V3A), R-CR15A.1 (/R/+3V3A), R-CR16A.1 (/R/+3V3A), R-CR17A.1 (/R/+3V3A), R-CR18A.1 (/R/+3V3A), R-CR19A.1 (/R/+3V3A), R-CR20A.1 (/R/+3V3A), R-CR21A.1 (/R/+3V3A), R-CR22A.1 (/R/+3V3A), R-CR23A.1 (/R/+3V3A), R-CR24A.1 (/R/+3V3A), R-CR25A.1 (/R/+3V3A), R-CR26A.1 (/R/+3V3A), R-CR27A.1 (/R/+3V3A), R-CR28A.1 (/R/+3V3A), R-CR29A.1 (/R/+3V3A), R-CR30A.1 (/R/+3V3A), R-CR31A.1 (/R/+3V3A), R-CR32A.1 (/R/+3V3A), R-CR33A.1 (/R/+3V3A), R-CR34A.1 (/R/+3V3A), R-CR35A.1 (/R/+3V3A), R-CR36A.1 (/R/+3V3A), R-HER1.1 (/R/+3V3A), R-HER2.1 (/R/+3V3A), R-HER3.1 (/R/+3V3A), R-HER4.1 (/R/+3V3A), R-HER5.1 (/R/+3V3A), R-HER6.1 (/R/+3V3A), R-HER7.1 (/R/+3V3A), R-HER8.1 (/R/+3V3A), R-HER9.1 (/R/+3V3A), R-HER10.1 (/R/+3V3A), R-HER11.1 (/R/+3V3A), R-HER12.1 (/R/+3V3A), R-HER13.1 (/R/+3V3A), R-HER14.1 (/R/+3V3A), R-HER15.1 (/R/+3V3A), R-HER16.1 (/R/+3V3A), R-HER17.1 (/R/+3V3A), R-HER18.1 (/R/+3V3A), R-HER19.1 (/R/+3V3A), R-HER20.1 (/R/+3V3A), R-HER21.1 (/R/+3V3A), R-HER22.1 (/R/+3V3A), R-HER23.1 (/R/+3V3A), R-HER24.1 (/R/+3V3A), R-HER25.1 (/R/+3V3A), R-HER26.1 (/R/+3V3A), R-HER27.1 (/R/+3V3A), R-HER28.1 (/R/+3V3A), R-HER29.1 (/R/+3V3A), R-HER30.1 (/R/+3V3A), R-HER31.1 (/R/+3V3A), R-HER32.1 (/R/+3V3A), R-HER33.1 (/R/+3V3A), R-HER34.1 (/R/+3V3A), R-HER35.1 (/R/+3V3A), R-HER36.1 (/R/+3V3A), R-JR1.1 (/R/+3V3A)
/R/ADC_R1: R-AMR1.3 (/R/ADC_R1), R-JR1.7 (/R/ADC_R1)
/R/ADC_R2: R-AMR2.3 (/R/ADC_R2), R-JR1.9 (/R/ADC_R2)
/R/ADC_R3: R-AMR3.3 (/R/ADC_R3), R-JR1.11 (/R/ADC_R3)
/R/ADC_R4: R-AMR4.3 (/R/ADC_R4), R-JR1.12 (/R/ADC_R4)
/R/ADC_R5: R-AMR5.3 (/R/ADC_R5), R-JR1.2 (/R/ADC_R5)
/R/HE_R01: R-AMR1.13 (/R/HE_R01), R-CR6B.1 (/R/HE_R01), R-HER6.3 (/R/HE_R01)
/R/HE_R02: R-AMR1.14 (/R/HE_R02), R-CR1B.1 (/R/HE_R02), R-HER1.3 (/R/HE_R02)
/R/HE_R03: R-AMR1.15 (/R/HE_R03), R-CR2B.1 (/R/HE_R03), R-HER2.3 (/R/HE_R03)
/R/HE_R04: R-AMR1.12 (/R/HE_R04), R-CR3B.1 (/R/HE_R04), R-HER3.3 (/R/HE_R04)
/R/HE_R05: R-AMR1.1 (/R/HE_R05), R-CR5B.1 (/R/HE_R05), R-HER5.3 (/R/HE_R05)
/R/HE_R06: R-AMR1.5 (/R/HE_R06), R-CR7B.1 (/R/HE_R06), R-HER7.3 (/R/HE_R06)
/R/HE_R07: R-AMR1.2 (/R/HE_R07), R-CR8B.1 (/R/HE_R07), R-HER8.3 (/R/HE_R07)
/R/HE_R09: R-AMR2.13 (/R/HE_R09), R-CR12B.1 (/R/HE_R09), R-HER12.3 (/R/HE_R09)
/R/HE_R10: R-AMR2.14 (/R/HE_R10), R-CR9B.1 (/R/HE_R10), R-HER9.3 (/R/HE_R10)
/R/HE_R11: R-AMR2.15 (/R/HE_R11), R-CR10B.1 (/R/HE_R11), R-HER10.3 (/R/HE_R11)
/R/HE_R12: R-AMR2.12 (/R/HE_R12), R-CR11B.1 (/R/HE_R12), R-HER11.3 (/R/HE_R12)
/R/HE_R13: R-AMR2.1 (/R/HE_R13), R-CR14B.1 (/R/HE_R13), R-HER14.3 (/R/HE_R13)
/R/HE_R14: R-AMR2.5 (/R/HE_R14), R-CR15B.1 (/R/HE_R14), R-HER15.3 (/R/HE_R14)
/R/HE_R15: R-AMR2.2 (/R/HE_R15), R-CR19B.1 (/R/HE_R15), R-HER19.3 (/R/HE_R15)
/R/HE_R16: R-AMR2.4 (/R/HE_R16), R-CR16B.1 (/R/HE_R16), R-HER16.3 (/R/HE_R16)
/R/HE_R17: R-AMR3.13 (/R/HE_R17), R-CR17B.1 (/R/HE_R17), R-HER17.3 (/R/HE_R17)
/R/HE_R18: R-AMR3.14 (/R/HE_R18), R-CR18B.1 (/R/HE_R18), R-HER18.3 (/R/HE_R18)
/R/HE_R19: R-AMR3.15 (/R/HE_R19), R-CR20B.1 (/R/HE_R19), R-HER20.3 (/R/HE_R19)
/R/HE_R20: R-AMR3.12 (/R/HE_R20), R-CR21B.1 (/R/HE_R20), R-HER21.3 (/R/HE_R20)
/R/HE_R21: R-AMR3.1 (/R/HE_R21), R-CR27B.1 (/R/HE_R21), R-HER27.3 (/R/HE_R21)
/R/HE_R22: R-AMR3.5 (/R/HE_R22), R-CR22B.1 (/R/HE_R22), R-HER22.3 (/R/HE_R22)
/R/HE_R23: R-AMR3.2 (/R/HE_R23), R-CR23B.1 (/R/HE_R23), R-HER23.3 (/R/HE_R23)
/R/HE_R24: R-AMR3.4 (/R/HE_R24), R-CR24B.1 (/R/HE_R24), R-HER24.3 (/R/HE_R24)
/R/HE_R25: R-AMR4.13 (/R/HE_R25), R-CR25B.1 (/R/HE_R25), R-HER25.3 (/R/HE_R25)
/R/HE_R26: R-AMR4.14 (/R/HE_R26), R-CR28B.1 (/R/HE_R26), R-HER28.3 (/R/HE_R26)
/R/HE_R27: R-AMR4.15 (/R/HE_R27), R-CR29B.1 (/R/HE_R27), R-HER29.3 (/R/HE_R27)
/R/HE_R28: R-AMR4.12 (/R/HE_R28), R-CR35B.1 (/R/HE_R28), R-HER35.3 (/R/HE_R28)
/R/HE_R29: R-AMR4.1 (/R/HE_R29), R-CR30B.1 (/R/HE_R29), R-HER30.3 (/R/HE_R29)
/R/HE_R30: R-AMR4.5 (/R/HE_R30), R-CR32B.1 (/R/HE_R30), R-HER32.3 (/R/HE_R30)
/R/HE_R31: R-AMR4.2 (/R/HE_R31), R-CR34B.1 (/R/HE_R31), R-HER34.3 (/R/HE_R31)
/R/HE_R32: R-AMR4.4 (/R/HE_R32), R-CR36B.1 (/R/HE_R32), R-HER36.3 (/R/HE_R32)
/R/HE_R33: R-AMR5.13 (/R/HE_R33), R-CR4B.1 (/R/HE_R33), R-HER4.3 (/R/HE_R33)
/R/HE_R34: R-AMR5.14 (/R/HE_R34), R-CR26B.1 (/R/HE_R34), R-HER26.3 (/R/HE_R34)
/R/HE_R35: R-AMR5.15 (/R/HE_R35), R-CR31B.1 (/R/HE_R35), R-HER31.3 (/R/HE_R35)
/R/HE_R36: R-AMR5.12 (/R/HE_R36), R-CR33B.1 (/R/HE_R36), R-HER33.3 (/R/HE_R36)
/R/MUX_A0: R-AMR1.11 (/R/MUX_A0), R-AMR2.11 (/R/MUX_A0), R-AMR3.11 (/R/MUX_A0), R-AMR4.11 (/R/MUX_A0), R-AMR5.11 (/R/MUX_A0), R-JR1.3 (/R/MUX_A0)
/R/MUX_A1: R-AMR1.10 (/R/MUX_A1), R-AMR2.10 (/R/MUX_A1), R-AMR3.10 (/R/MUX_A1), R-AMR4.10 (/R/MUX_A1), R-AMR5.10 (/R/MUX_A1), R-JR1.4 (/R/MUX_A1)
/R/MUX_A2: R-AMR1.9 (/R/MUX_A2), R-AMR2.9 (/R/MUX_A2), R-AMR3.9 (/R/MUX_A2), R-AMR4.9 (/R/MUX_A2), R-AMR5.9 (/R/MUX_A2), R-JR1.5 (/R/MUX_A2)
/R/RGB_R: R-DR1.2 (/R/RGB_R), R-JR1.10 (/R/RGB_R)
/R/RGB_R_01: R-DR1.4 (/R/RGB_R_01), R-DR2.2 (/R/RGB_R_01)
/R/RGB_R_02: R-DR2.4 (/R/RGB_R_02), R-DR3.2 (/R/RGB_R_02)
/R/RGB_R_03: R-DR3.4 (/R/RGB_R_03), R-DR4.2 (/R/RGB_R_03), R-DR33.2 (/R/RGB_R_03)
/R/RGB_R_04: R-DR4.4 (/R/RGB_R_04), R-DR5.2 (/R/RGB_R_04), R-DR33.4 (/R/RGB_R_04), R-RBPR5.1 (/R/RGB_R_04)
/R/RGB_R_05: R-DR5.4 (/R/RGB_R_05), R-DR6.2 (/R/RGB_R_05), R-RBPR5.2 (/R/RGB_R_05)
/R/RGB_R_06: R-DR6.4 (/R/RGB_R_06), R-DR7.2 (/R/RGB_R_06)
/R/RGB_R_07: R-DR7.4 (/R/RGB_R_07), R-DR8.2 (/R/RGB_R_07)
/R/RGB_R_08: R-DR8.4 (/R/RGB_R_08), R-DR9.2 (/R/RGB_R_08)
/R/RGB_R_09: R-DR9.4 (/R/RGB_R_09), R-DR10.2 (/R/RGB_R_09)
/R/RGB_R_10: R-DR10.4 (/R/RGB_R_10), R-DR11.2 (/R/RGB_R_10)
/R/RGB_R_11: R-DR11.4 (/R/RGB_R_11), R-DR12.2 (/R/RGB_R_11)
/R/RGB_R_12: R-DR12.4 (/R/RGB_R_12), R-DR13.2 (/R/RGB_R_12)
/R/RGB_R_13: R-DR13.4 (/R/RGB_R_13), R-DR14.2 (/R/RGB_R_13)
/R/RGB_R_14: R-DR14.4 (/R/RGB_R_14), R-DR15.2 (/R/RGB_R_14)
/R/RGB_R_15: R-DR15.4 (/R/RGB_R_15), R-DR16.2 (/R/RGB_R_15)
/R/RGB_R_16: R-DR16.4 (/R/RGB_R_16), R-DR17.2 (/R/RGB_R_16)
/R/RGB_R_17: R-DR17.4 (/R/RGB_R_17), R-DR18.2 (/R/RGB_R_17)
/R/RGB_R_18: R-DR18.4 (/R/RGB_R_18), R-DR19.2 (/R/RGB_R_18)
/R/RGB_R_19: R-DR19.4 (/R/RGB_R_19), R-DR20.2 (/R/RGB_R_19)
/R/RGB_R_20: R-DR20.4 (/R/RGB_R_20), R-DR21.2 (/R/RGB_R_20), R-DR34.2 (/R/RGB_R_20)
/R/RGB_R_21: R-DR21.4 (/R/RGB_R_21), R-DR22.2 (/R/RGB_R_21), R-DR34.4 (/R/RGB_R_21)
/R/RGB_R_22: R-DR22.4 (/R/RGB_R_22), R-DR23.2 (/R/RGB_R_22)
/R/RGB_R_23: R-DR23.4 (/R/RGB_R_23), R-DR24.2 (/R/RGB_R_23), R-RBPR24.1 (/R/RGB_R_23)
/R/RGB_R_24: R-DR24.4 (/R/RGB_R_24), R-DR25.2 (/R/RGB_R_24), R-RBPR24.2 (/R/RGB_R_24)
/R/RGB_R_25: R-DR25.4 (/R/RGB_R_25), R-DR26.2 (/R/RGB_R_25)
/R/RGB_R_26: R-DR26.4 (/R/RGB_R_26), R-DR27.2 (/R/RGB_R_26)
/R/RGB_R_27: R-DR27.4 (/R/RGB_R_27), R-DR28.2 (/R/RGB_R_27)
/R/RGB_R_28: R-DR28.4 (/R/RGB_R_28), R-DR29.2 (/R/RGB_R_28)
/R/RGB_R_29: R-DR29.4 (/R/RGB_R_29), R-DR36.2 (/R/RGB_R_29)
/R/RGB_R_30: R-DR31.2 (/R/RGB_R_30), R-DR36.4 (/R/RGB_R_30), R-RBPR31.1 (/R/RGB_R_30)
/R/RGB_R_31: R-DR31.4 (/R/RGB_R_31), R-DR32.2 (/R/RGB_R_31), R-RBPR31.2 (/R/RGB_R_31)
/R/RGB_R_END: R-DR32.4 (/R/RGB_R_END)
/R/VBUS: R-CRGBR1.1 (/R/VBUS), R-CRGBR2.1 (/R/VBUS), R-CRGBR3.1 (/R/VBUS), R-CRGBR4.1 (/R/VBUS), R-CRGBR5.1 (/R/VBUS), R-CRGBR6.1 (/R/VBUS), R-CRGBR7.1 (/R/VBUS), R-CRGBR8.1 (/R/VBUS), R-CRGBR9.1 (/R/VBUS), R-CRGBR10.1 (/R/VBUS), R-CRGBR11.1 (/R/VBUS), R-CRGBR12.1 (/R/VBUS), R-CRGBR13.1 (/R/VBUS), R-CRGBR14.1 (/R/VBUS), R-CRGBR15.1 (/R/VBUS), R-CRGBR16.1 (/R/VBUS), R-CRGBR17.1 (/R/VBUS), R-CRGBR18.1 (/R/VBUS), R-CRGBR19.1 (/R/VBUS), R-CRGBR20.1 (/R/VBUS), R-CRGBR21.1 (/R/VBUS), R-CRGBR22.1 (/R/VBUS), R-CRGBR23.1 (/R/VBUS), R-CRGBR24.1 (/R/VBUS), R-CRGBR25.1 (/R/VBUS), R-CRGBR26.1 (/R/VBUS), R-CRGBR27.1 (/R/VBUS), R-CRGBR28.1 (/R/VBUS), R-CRGBR29.1 (/R/VBUS), R-CRGBR31.1 (/R/VBUS), R-CRGBR32.1 (/R/VBUS), R-CRGBR33.1 (/R/VBUS), R-CRGBR34.1 (/R/VBUS), R-CRGBR36.1 (/R/VBUS), R-DR1.3 (/R/VBUS), R-DR2.3 (/R/VBUS), R-DR3.3 (/R/VBUS), R-DR4.3 (/R/VBUS), R-DR5.3 (/R/VBUS), R-DR6.3 (/R/VBUS), R-DR7.3 (/R/VBUS), R-DR8.3 (/R/VBUS), R-DR9.3 (/R/VBUS), R-DR10.3 (/R/VBUS), R-DR11.3 (/R/VBUS), R-DR12.3 (/R/VBUS), R-DR13.3 (/R/VBUS), R-DR14.3 (/R/VBUS), R-DR15.3 (/R/VBUS), R-DR16.3 (/R/VBUS), R-DR17.3 (/R/VBUS), R-DR18.3 (/R/VBUS), R-DR19.3 (/R/VBUS), R-DR20.3 (/R/VBUS), R-DR21.3 (/R/VBUS), R-DR22.3 (/R/VBUS), R-DR23.3 (/R/VBUS), R-DR24.3 (/R/VBUS), R-DR25.3 (/R/VBUS), R-DR26.3 (/R/VBUS), R-DR27.3 (/R/VBUS), R-DR28.3 (/R/VBUS), R-DR29.3 (/R/VBUS), R-DR31.3 (/R/VBUS), R-DR32.3 (/R/VBUS), R-DR33.3 (/R/VBUS), R-DR34.3 (/R/VBUS), R-DR36.3 (/R/VBUS), R-JR1.6 (/R/VBUS)

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
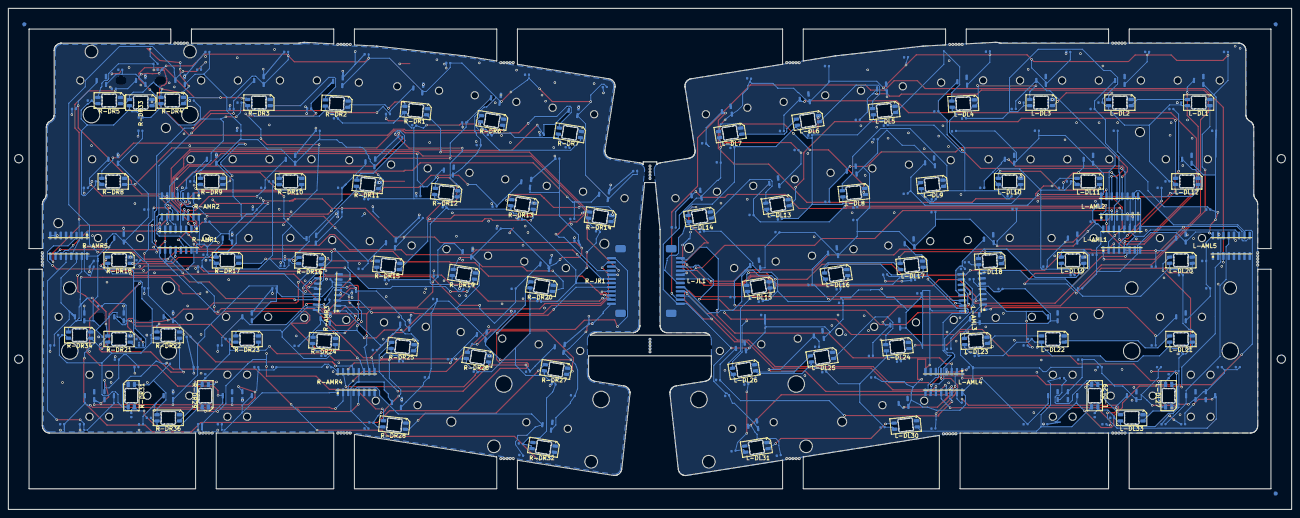
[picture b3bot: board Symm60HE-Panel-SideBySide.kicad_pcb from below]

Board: 2 copper layers, 310.2 x 121.1 mm, 463 parts (366 on the bottom side), 154 nets.

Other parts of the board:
FID1, FID2, FID3: FIDUCIAL_1MM_BCU; Fiducial_1mm_BCu
L-MHL1, L-MHL2, L-MHL3, L-MHL4: M2_NPTH; MountingHole_2.2mm_M2_NPTH
L-SL1, L-SL2: STAB_MX; STABILIZER_MX_2U
MB1, MB2, MB3, MB4, MB5, MB6, MB7, MB8, MB9, MB10, MB11, MB12, MB13, MB14, MB15, MB16, MB17, MB18, MB19, MB20, MB21, MB22, MB23, MB24, MB25, MB26, MB27, MB28, MB29, MB30, MB31, MB32, MB33, MB34, MB35, MB36, MB37, MB38, MB39, MB40, MB41, MB42, MB43, MB44, MB45, MB46, MB47, MB48, MB49, MB50, MB51, MB52, MB53, MB54, MB55, MB56, MB57, MB58, MB59, MB60, MB61, MB62, MB63, MB64, MB65, MB66, MB67, MB68, MB69, MB70, MB71, MB72, MB73, MB74, MB75, MB76, MB77, MB78, MB79, MB80: MOUSE_BITE_0.5MM; MouseBite_0.5mm
R-MHR1, R-MHR2, R-MHR3, R-MHR4: M2_NPTH; MountingHole_2.2mm_M2_NPTH
R-SR1, R-SR2, R-SR3: STAB_MX; STABILIZER_MX_2U
TH1, TH2, TH3, TH4: TOOLING_HOLE_2MM; ToolingHole_2mm_NPTH
